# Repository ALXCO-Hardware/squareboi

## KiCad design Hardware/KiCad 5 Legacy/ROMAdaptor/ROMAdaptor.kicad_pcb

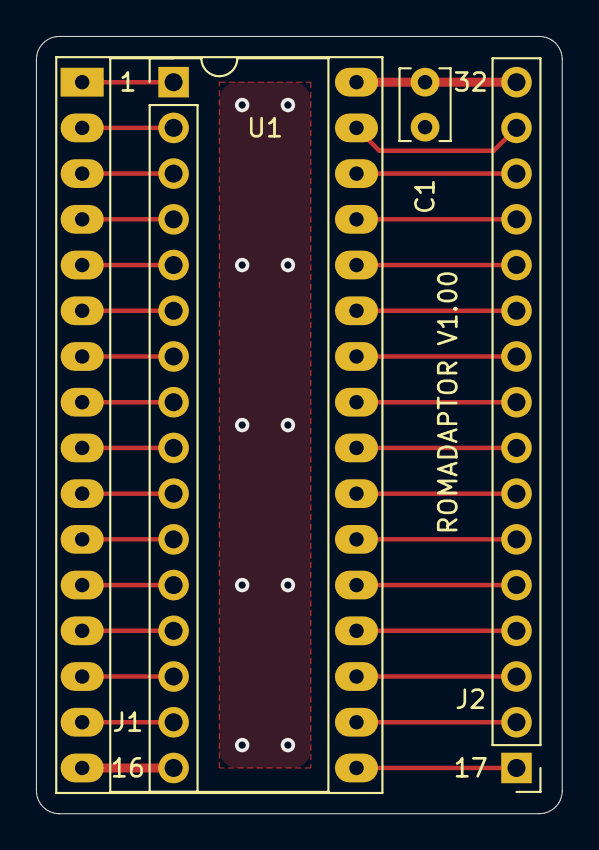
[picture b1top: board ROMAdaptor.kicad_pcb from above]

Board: 2 copper layers, 29.2 x 43.2 mm, 4 parts (0 on the bottom side), 32 nets.

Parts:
C1: 100n; C_Disc_D3.8mm_W2.6mm_P2.50mm
J1, J2: Conn_01x16; PinHeader_1x16_P2.54mm_Vertical
U1: SST39SF040; DIP-32_W15.24mm_Socket_LongPads

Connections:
+5V: C1.1, J2.16, U1.32
/A0: J1.12, U1.12
/A1: J1.11, U1.11
/A2: J1.10, U1.10
/A3: J1.9, U1.9
/A4: J1.8, U1.8
/A5: J1.7, U1.7
/A6: J1.6, U1.6
/A7: J1.5, U1.5
/A8: J2.11, U1.27
/A9: J2.10, U1.26
/A10: J2.7, U1.23
/A11: J2.9, U1.25
/A12: J1.4, U1.4
/A13: J2.12, U1.28
/A14: J2.13, U1.29
/A15: J1.3, U1.3
/A16: J1.2, U1.2
/A17: J2.14, U1.30
/A18: J1.1, U1.1
/D0: J1.13, U1.13
/D1: J1.14, U1.14
/D2: J1.15, U1.15
/D3: J2.1, U1.17
/D4: J2.2, U1.18
/D5: J2.3, U1.19
/D6: J2.4, U1.20
/D7: J2.5, U1.21
/RD_N: J2.8, U1.24
/ROMCS_N: J2.6, U1.22
/WR_N: J2.15, U1.31
GND: C1.2, J1.16, U1.16

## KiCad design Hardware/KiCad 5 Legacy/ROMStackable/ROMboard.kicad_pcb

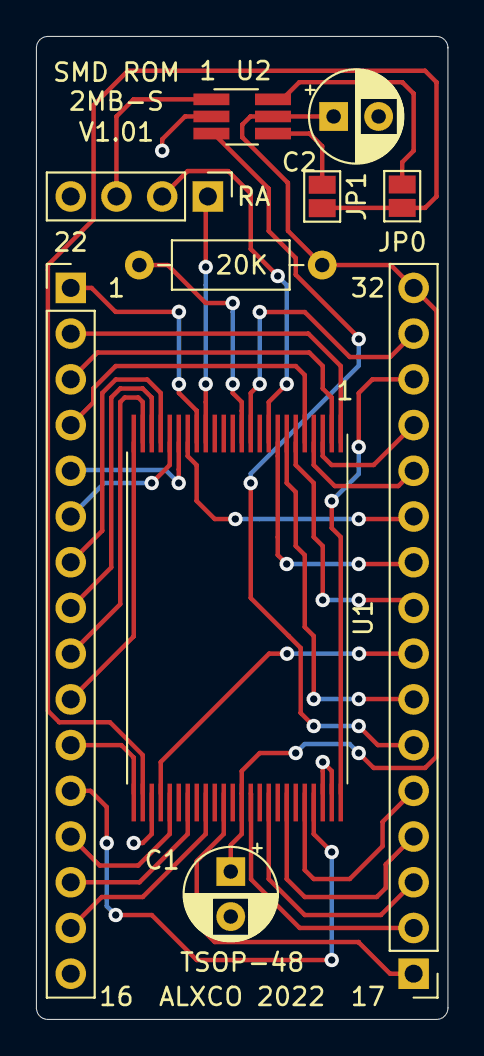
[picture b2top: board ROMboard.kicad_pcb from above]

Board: 2 copper layers, 22.9 x 54.6 mm, 10 parts (0 on the bottom side), 39 nets.

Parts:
C1, C2: 100n; CP_Radial_D5.0mm_P2.50mm
J0, J1: Conn_01x16; PinHeader_1x16_P2.54mm_Vertical
J2: Conn_01x04; PinHeader_1x04_P2.54mm_Vertical
JP0, JP1: Jumper_2_Open; SolderJumper-2_P1.3mm_Open_Pad1.0x1.5mm
R1: 20K; R_Axial_DIN0207_L6.3mm_D2.5mm_P10.16mm_Horizontal
U1: M29F160; TSOP-I-48_18.4x12mm_P0.5mm
U2: 74LVC1G19; TSOT-23-6_HandSoldering

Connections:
+5V: C1.1, C2.1, J1.16, R1.1, U1.37, U2.5
/A0: J0.12, U1.45
/A1: J0.11, U1.25
/A2: J0.10, U1.24
/A3: J0.9, U1.23
/A4: J0.8, U1.22
/A5: J0.7, U1.21
/A6: J0.6, U1.20
/A7: J0.5, U1.19
/A8: J1.11, U1.18
/A9: J1.10, U1.8
/A10: J1.7, U1.7
/A11: J1.9, U1.6
/A12: J0.4, U1.5
/A13: J1.12, U1.4
/CE_N: J1.6, U2.3
/CE_OUT_N: JP0.2, JP1.2, U1.26
/D0: J0.13, U1.29
/D1: J0.14, U1.31
/D2: J0.15, U1.33
/D3: J1.1, U1.35
/D4: J1.2, U1.38
/D5: J1.3, U1.40
/D6: J1.4, U1.42
/D7: J1.5, U1.44
/RA14: J1.13, U1.3
/RA15: J0.3, U1.2
/RA16: J0.2, U1.1
/RA17: J1.14, U1.48
/RA18: J0.1, U1.17
/RA19: J2.1, U1.16
/RA20: J2.2, U1.9
/RA21: J2.3, U2.1
/RD_N: J1.8, U1.28
/ROMWR_N: J1.15, U1.11
/RST_N: R1.2, U1.12
GND: C1.2, C2.2, J0.16, U1.27, U1.46, U1.47, U2.2
unnamed: JP0.1, U2.6
unnamed: JP1.1, U2.4
